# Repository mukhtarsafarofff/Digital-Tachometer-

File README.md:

(ENG) A Tachometer is a device which measures the speed of a rotating object like an electric motor or a crank shaft of a vehicle engine. Speed of an electric motor is determined by the number of revolutions made by the motor in one minute. In other words, speed is measured in RPM (Revolutions per Minute). Here, in this project, we designed a simple Non – Contact or Contactless Digital Tachometer using 8051 Microcontroller, which can measure speed with an accuracy of 1 rev/sec.The basic principle behind the Contactless Digital Tachometer involves a simple embedded system with a sensor, a controller and an actuator.The sensor used here is Infrared (IR) transmitter – receiver pair, the controller used is the 8051 Microcontroller loaded with a compiled code and the actuator is a display device, for displaying the speed of the motor.The sensor senses the speed of the motor without actually being in contact with it by the principle of light transmission and reflection and generates a signal. This signal is converted into an electric signal and fed to the microcontroller, which is programmed to calculate the speed in terms of number of motor revolutions in one minute. This speed is displayed on the 7-segment display.  It basically works on the principle of retro reflective scanning, wherein a light source device like LED transmits light signal to the retro reflective target device which reflects the light, which is in turn received by the light detector.  The sensor circuit consists of an IR transmitter and an IR receiver. An IR LED is used as the transmitter and a photo diode is used as the receiver.  A reflective type of IR sensor is used in this project. In this type, the IR transmitter and receiver are placed side -by – side.When the IR sensor is powered, the IR transmitter starts emitting IR rays.  A motor is placed in front of the IR sensor, with its shafted marked with a white dot. As the motor shaft rotates such that the white spots comes in contact with the sensor, the IR rays are reflected by the dot and falls on the IR receiver.   The photo diode, which is used as the IR receiver, starts conducting whenever the IR rays are reflected.

(DEU) Ein Drehzahlmesser ist ein Gerät, das die Geschwindigkeit eines rotierenden Objekts wie eines Elektromotors oder einer Kurbelwelle eines Fahrzeugmotors misst. Die Geschwindigkeit eines Elektromotors wird durch die Anzahl der Umdrehungen bestimmt, die der Motor in einer Minute macht.Mit anderen Worten, die Geschwindigkeit wird in U/min (Umdrehungen pro Minute) gemessen.In diesem Projekt haben wir einen einfachen berührungslosen Digitaltachometer oder berührungslosen Digitaltachometer mit einem 8051-Mikrocontroller entwickelt, der eine Geschwindigkeit mit einer Genauigkeit von 1 Umdrehung/Sekunde messen kann.Dieses Signal wird in ein elektrisches Signal umgewandelt und dem Mikrocontroller zugeführt, der programmiert ist, um die Geschwindigkeit in Form der Anzahl der Motorumdrehungen pro Minute zu berechnen.Diese Geschwindigkeit wird auf der 7-Segment-Anzeige angezeigt.Es funktioniert im Wesentlichen nach dem Prinzip des retroreflektierenden Scannens, bei dem ein Lichtquellengerät wie eine LED Lichtsignale an das retroreflektierende Zielgerät sendet, das das Licht reflektiert, das wiederum vom Lichtdetektor empfangen wird.Die Sensorschaltung besteht aus einem IR-Sender und einem IR-Empfänger. Eine IR-LED wird als Sender verwendet und eine Fotodiode als Empfänger. In diesem Projekt wird ein reflektiver Typ von IR-Sensor verwendet. Bei dieser Art werden der IR-Sender und -Empfänger seitlich nebeneinander platziert. Wenn der IR-Sensor eingeschaltet ist, beginnt der IR-Sender Infrarotstrahlen auszusenden. Ein Motor ist vor dem IR-Sensor platziert, dessen Welle mit einem weißen Punkt markiert ist. Ein Motor wird vor den IR-Sensor platziert, wobei seine Welle mit einem weißen Punkt markiert ist. Wenn sich die Motorwelle so dreht, dass der weiße Punkt den Sensor berührt, werden die IR-Strahlen

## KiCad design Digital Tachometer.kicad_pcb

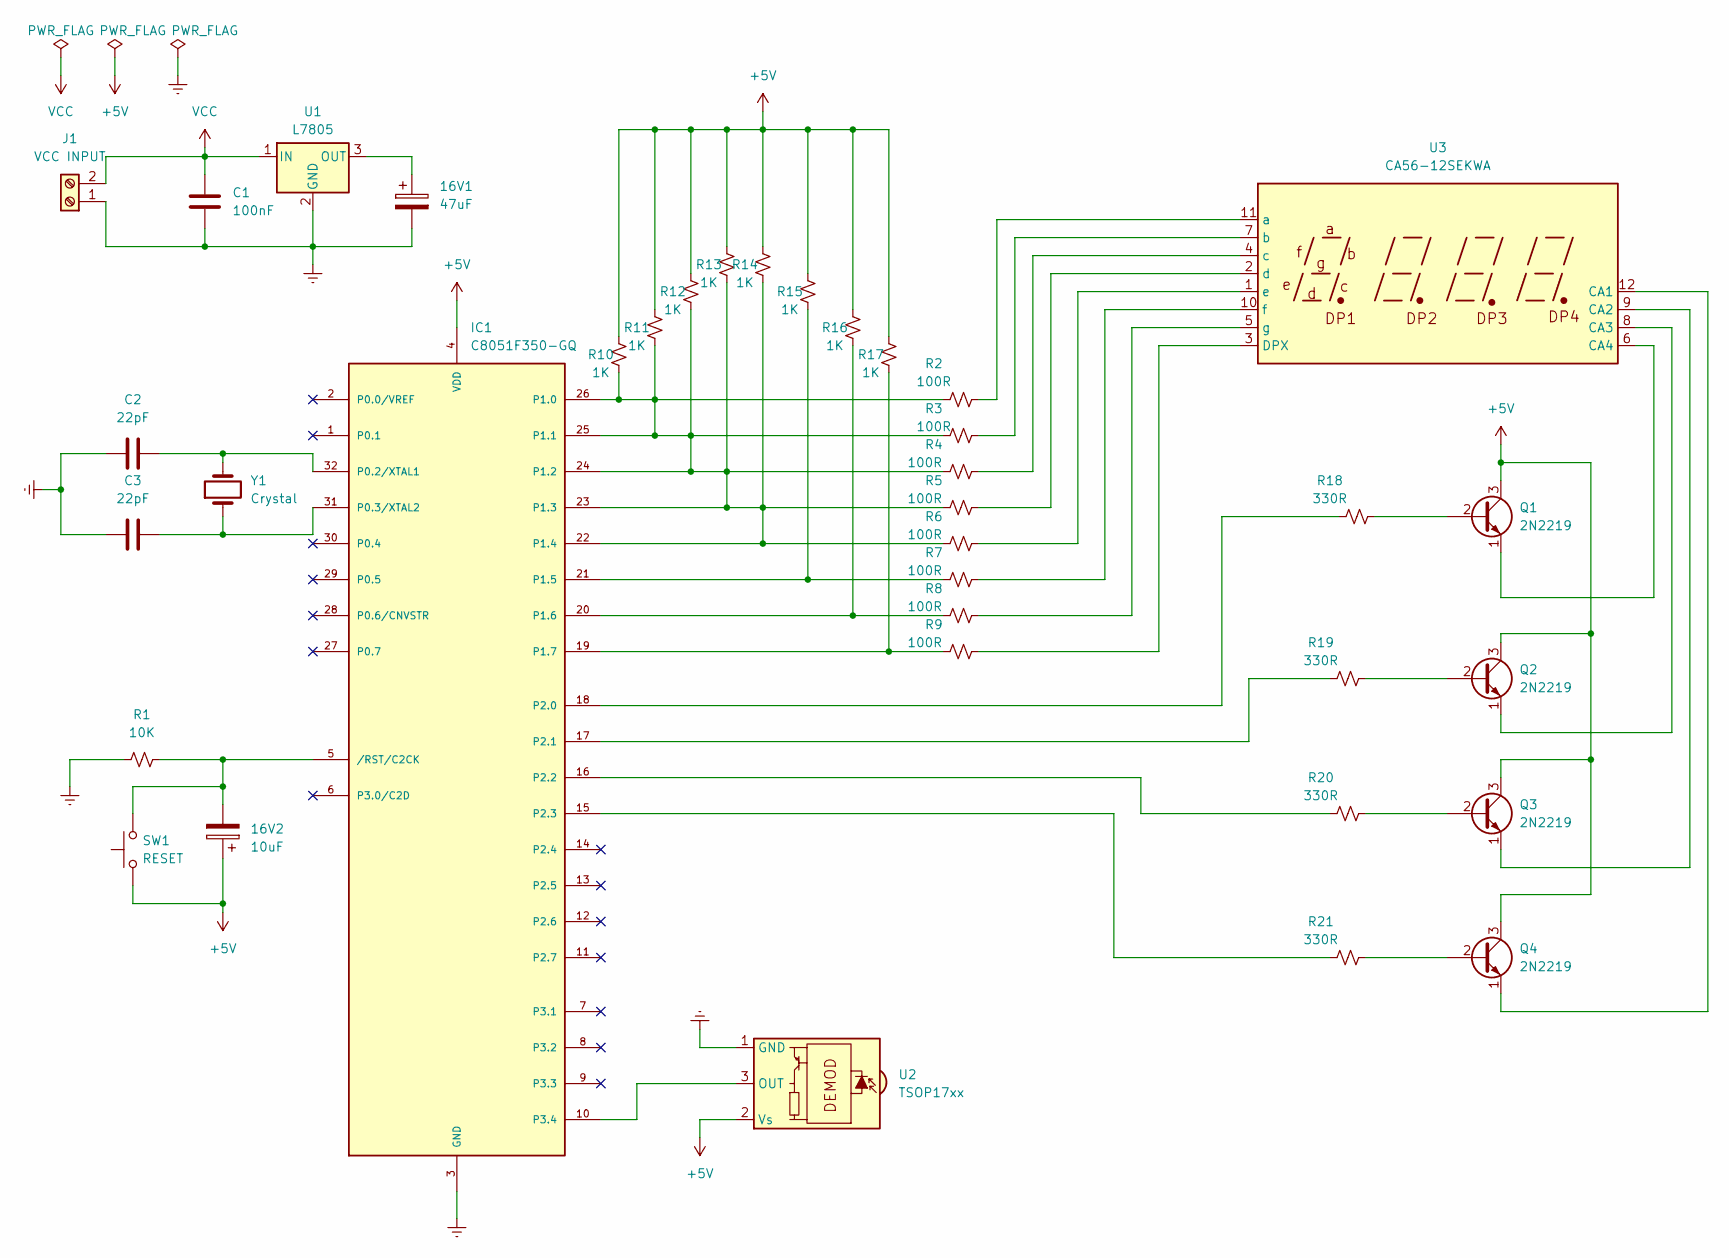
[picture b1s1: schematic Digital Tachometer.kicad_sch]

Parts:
16V1: 47uF; CP_Radial_D12.5mm_P7.50mm
16V2: 10uF; CP_Radial_D12.5mm_P7.50mm
C1: 100nF; C_Disc_D8.0mm_W5.0mm_P7.50mm
C2, C3: 22pF; C_Disc_D8.0mm_W5.0mm_P7.50mm
IC1: C8051F350-GQ; DIP-40_W15.24mm
J1: VCC INPUT; TerminalBlock_Phoenix_MKDS-1,5-2-5.08_1x02_P5.08mm_Horizont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
Q1, Q2, Q3, Q4: 2N2219; TO-39-3
R1: 10K; R_Axial_DIN0207_L6.3mm_D2.5mm_P15.24mm_Horizontal
R2, R3, R4, R5, R6, R7, R8, R9: 100R; R_Axial_DIN0207_L6.3mm_D2.5mm_P15.24mm_Horizontal
R10, R11, R12, R13, R14, R15, R16, R17: 1K; R_Axial_DIN0207_L6.3mm_D2.5mm_P15.24mm_Horizontal
R18, R19, R20, R21: 330R; R_Axial_DIN0207_L6.3mm_D2.5mm_P15.24mm_Horizontal
SW1: RESET; SW_Tactile_Straight_KSA0Axx1LFTR
U1: L7805; TO-220-3_Vertical
U2: TSOP17xx; Vishay_CAST-3Pin
U3: CA56-12SEKWA
Y1: Crystal; Crystal_HC49-4H_Vertical

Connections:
+5V: 16V2.1, IC1.4 (VDD), Q1.3 (C), Q2.3 (C), Q3.3 (C), Q4.3 (C), R10.1, R11.1, R12.1, R13.1, R14.1, R15.1, R16.1, R17.1, SW1.1, U2.2 (Vs)
Earth: 16V1.2, C1.2, C2.2, C3.2, IC1.3 (GND), J1.1, R1.1, U1.2 (GND), U2.1 (GND)
unnamed: C2.1, IC1.32 (P0.2/XTAL1), Y1.2
unnamed: C3.1, IC1.31 (P0.3/XTAL2), Y1.1
unnamed: IC1.22 (P1.4), IC1.23 (P1.3), IC1.24 (P1.2), IC1.25 (P1.1), IC1.26 (P1.0), R2.1, R3.1, R4.1, R5.1, R6.1, R10.2, R11.2, R12.2, R13.2, R14.2
unnamed: IC1.21 (P1.5), R7.1, R15.2
unnamed: IC1.20 (P1.6), R8.1, R16.2
unnamed: IC1.19 (P1.7), R9.1, R17.2
unnamed: IC1.18 (P2.0), R18.1
unnamed: IC1.17 (P2.1), R19.1
unnamed: IC1.16 (P2.2), R20.1
unnamed: IC1.15 (P2.3), R21.1
unnamed: IC1.10 (P3.4), U2.3 (OUT)
unnamed: 16V2.2, IC1.5 (/RST/C2CK), R1.2, SW1.2
unnamed: Q1.2 (B), R18.2
unnamed: Q1.1 (E), U3.6 (CA4)
unnamed: Q2.2 (B), R19.2
unnamed: Q2.1 (E), U3.8 (CA3)
unnamed: Q3.2 (B), R20.2
unnamed: Q3.1 (E), U3.9 (CA2)
unnamed: Q4.2 (B), R21.2
unnamed: Q4.1 (E), U3.12 (CA1)
unnamed: 16V1.1, U1.3 (OUT)
unnamed: R9.2, U3.3 (DPX)
unnamed: R2.2, U3.11 (a)
unnamed: R3.2, U3.7 (b)
unnamed: R4.2, U3.4 (c)
unnamed: R5.2, U3.2 (d)
unnamed: R6.2, U3.1 (e)
unnamed: R7.2, U3.10 (f)
unnamed: R8.2, U3.5 (g)
VCC: C1.1, J1.2, U1.1 (IN)

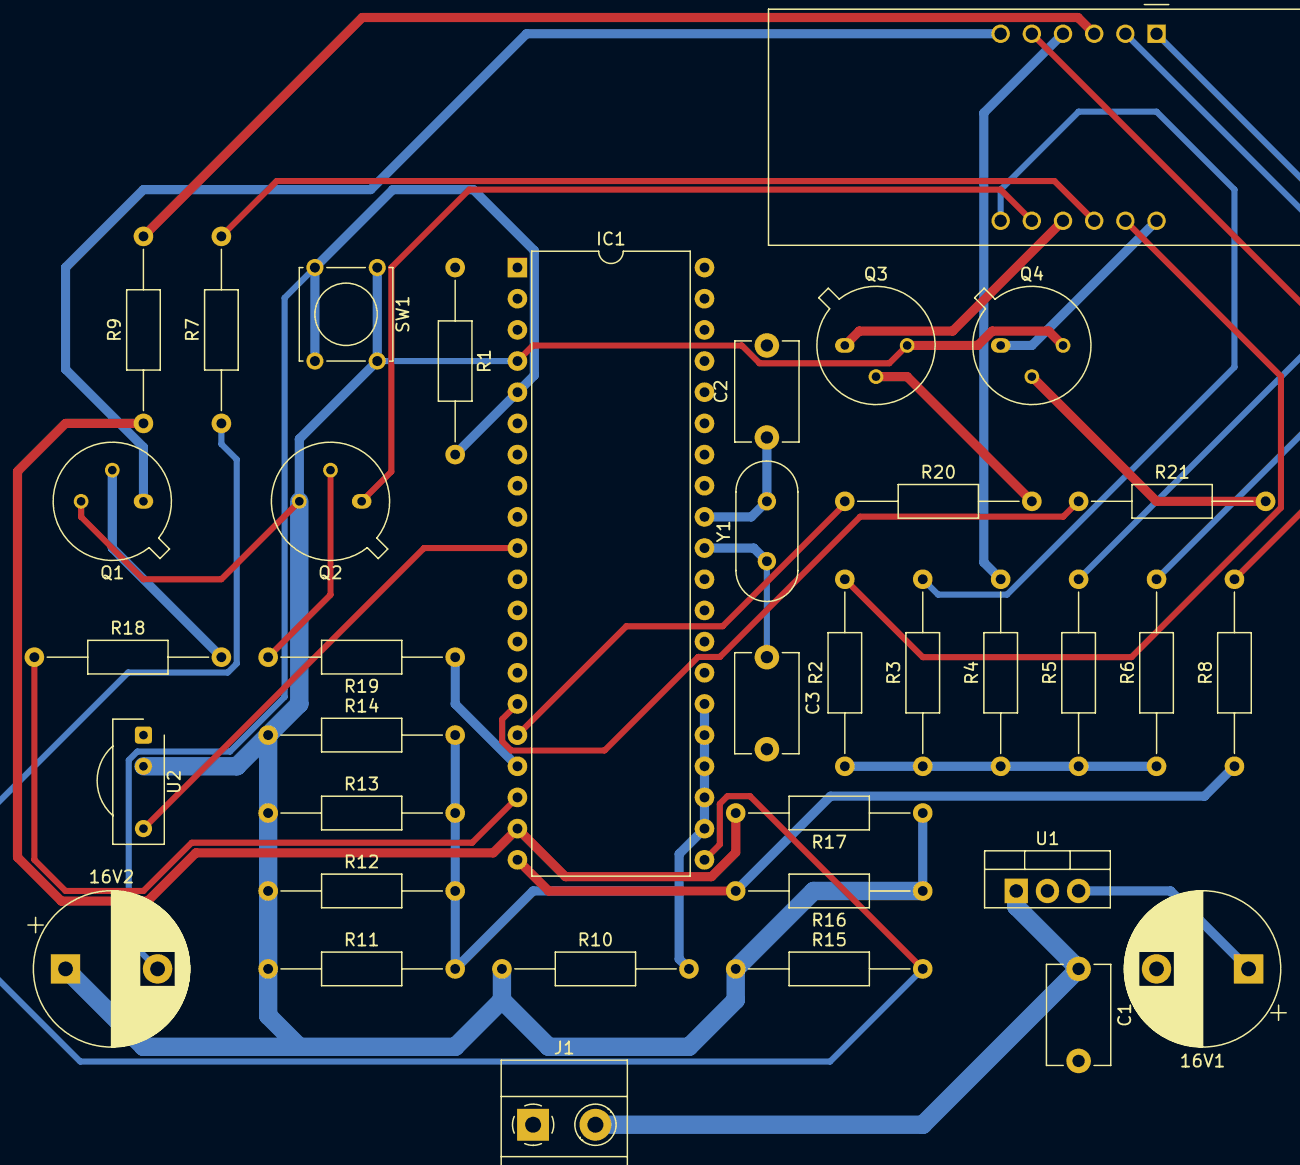
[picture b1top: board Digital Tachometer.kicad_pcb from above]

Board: 2 copper layers, 37 parts (0 on the bottom side), 32 nets.

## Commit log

2024-04-16 Digital Tachometer is accomplished
